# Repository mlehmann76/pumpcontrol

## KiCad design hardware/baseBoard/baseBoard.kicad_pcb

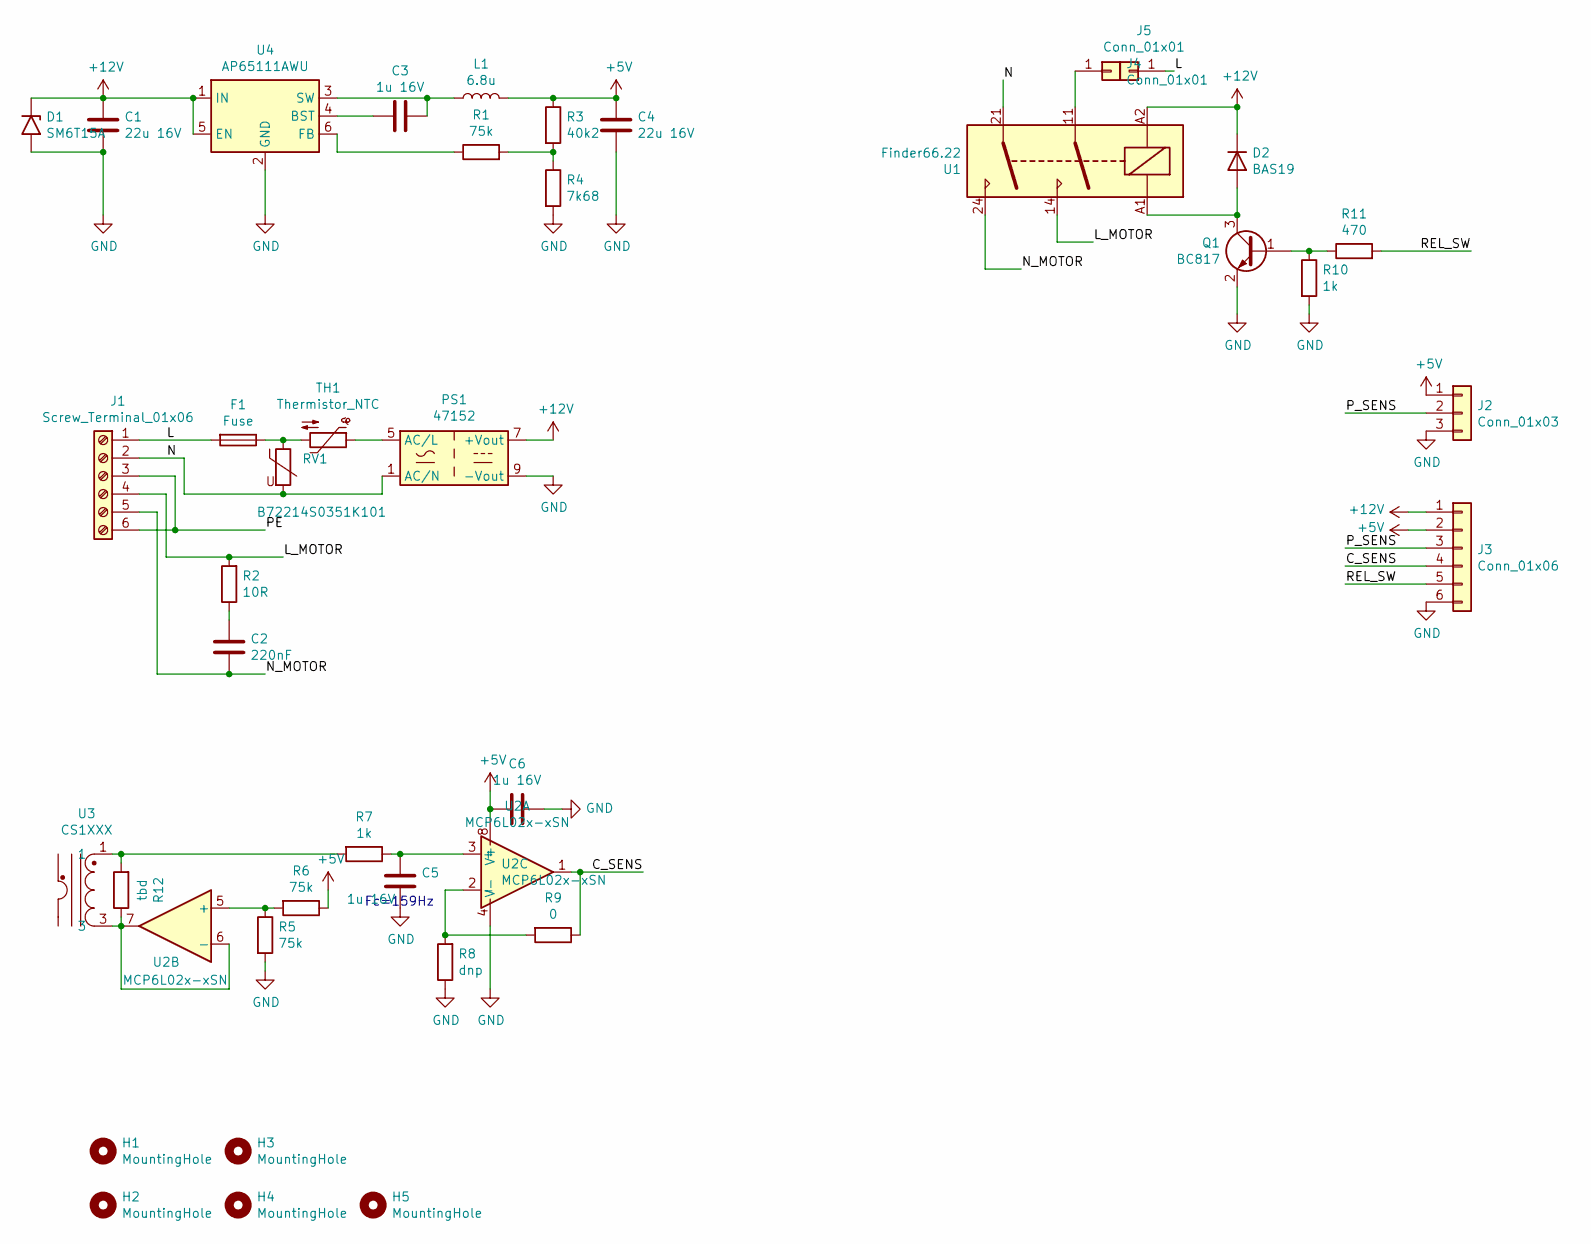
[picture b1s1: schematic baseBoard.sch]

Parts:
C1, C4: 22u 16V; C_1206_3216Metric
C2: 220nF; C_Rect_L18.0mm_W8.0mm_P15.00mm_FKS3_FKP3
C3, C5, C6: 1u 16V; C_0603_1608Metric
D1: SM6T15A; D_SMB
D2: BAS19; SOT-23
F1: Fuse; Fuseholder_Cylinder-5x20mm_Stelvio-Kontek_PTF78_Horizontal_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
H1, H2, H3, H4, H5: MountingHole; MountingHole_4.3mm_M4
J1: Screw_Terminal_01x06; DG58C-A
J2: Conn_01x03; PhoenixContact_MCV_1,5_3-G-3.81_1x03_P3.81mm_Vertical
J3: Conn_01x06; 2178710-6
J4, J5: Conn_01x01; Pin_D1.4mm_L8.5mm_W2.8mm_FlatFork
L1: 6.8u; L_Taiyo-Yuden_NR-50xx
PS1: 47152; Converter_ACDC_Hahn_HS-400xx_THT
Q1: BC817; SOT-23
R1, R5, R6: 75k; R_0603_1608Metric
R2: 10R; R_Axial_DIN0918_L18.0mm_D9.0mm_P7.62mm_Vertical
R3: 40k2; R_0603_1608Metric
R4: 7k68; R_0603_1608Metric
R7, R10: 1k; R_0603_1608Metric
R8: dnp; R_0603_1608Metric
R9: 0; R_0603_1608Metric
R11: 470; R_0603_1608Metric
R12: tbd; R_0603_1608Metric
RV1: B72214S0351K101; RV_Disc_D15.5mm_W6.3mm_P7.5mm
TH1: Thermistor_NTC; R_Axial_DIN0207_L6.3mm_D2.5mm_P10.16mm_Horizontal
U1: Finder66.22; Finder_66.22_x600
U2: MCP6L02x-xSN; SOIC-8_3.9x4.9mm_P1.27mm
U3: CS1XXX; CS1xxx
U4: AP65111AWU; TSOT-23-6

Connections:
+5V: C4.1, C6.2, J2.1, J3.2, L1.2, R3.1, R6.1, U2.8 (V+)
+12V: C1.1, D1.1 (A1), D2.3 (K), J3.1, PS1.7 (+Vout), U1.A2, U4.1 (IN), U4.5 (EN)
/C_SENS: J3.4, R9.1, U2.1
/L: F1.2, J1.1, J5.1
/L_MOTOR: J1.4, R2.2, U1.14
/N: J1.2, PS1.1 (AC/N), RV1.2, U1.21
/N_MOTOR: C2.2, J1.5, U1.24
/PE: J1.3, J1.6
/P_SENS: J2.2, J3.3
/REL_SW: J3.5, R11.2
GND: C1.2, C4.2, C5.2, C6.1, D1.2 (A2), J2.3, J3.6, PS1.9 (-Vout), Q1.2 (E), R4.2, R5.2, R8.1, R10.2, U2.4 (V-), U4.2 (GND)
unnamed: C2.1, R2.1
unnamed: C3.1, L1.1, U4.3 (SW)
unnamed: C3.2, U4.4 (BST)
unnamed: C5.1, R7.1, U2.3 (+)
unnamed: D2.1 (A), Q1.3 (C), U1.A1
unnamed: F1.1, RV1.1, TH1.2
unnamed: J4.1, U1.11
unnamed: PS1.5 (AC/L), TH1.1
unnamed: Q1.1 (B), R10.1, R11.1
unnamed: R1.1, U4.6 (FB)
unnamed: R1.2, R3.2, R4.1
unnamed: R5.1, R6.2, U2.5 (+)
unnamed: R8.2, R9.2, U2.2 (-)
unnamed: R12.1, U2.6 (-), U2.7, U3.3
unnamed: R7.2, R12.2, U3.1

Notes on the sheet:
Fc=159Hz

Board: 2 copper layers, 40 parts (0 on the bottom side), 26 nets, no tracks yet.

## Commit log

2021-04-08 initial
2021-04-10 sch / pcb update
